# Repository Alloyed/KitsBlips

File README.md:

# KitsBlips

Monorepo for my Eurorack/synthesizer hobby projects! (that's me, I'm kit)

Everything is always in a state of "not-quite-finished". if something is unclear or unusable in its current state, and you want to use it, feel free to open an issue or contact me.

For technical reasons, this project is ordered by toolset and not by module. this means the full source for a single module may be across multiple folders! Sorry.

unless otherwise listed, all code is MIT licensed. All hardware designs and graphics (kicad, svg etc) are CC-BY-SA 4.0.

## Building/Installing

Each project/folder has a specific readme that includes extra steps if necessary, but in general, builds are managed using cmake.

```
$ mkdir -p <folder>/build && cd <folder>/build
$ cmake .. -DCMAKE_BUILD_TYPE=<build type: Debug, MinSizeRel, RelWithDebInfo>
$ cmake --build . --config=<the build type>
$ cmake --install . --prefix <location> # if the target supports installation
$ ctest # if the target has unit tests
```

once you have all your configurations set up, you can quickly rebuild all/run tests using `rebuild-all.sh`.

## Projects

For Hardware:

- [/daisy](daisy/README.md)
  - DSP code for hardware modules, using the Daisy microcontroller.
- [/kicad](kicad/README.md)
  - Hardware design files

For VCV Rack:

- [/vcvrack](daisy/README.md)
  - Modules for VCV Rack

For DAWS:

- [/daw](clap/README.md)
  - Modules for DAWS (VST3/CLAP plugins)
- [/clapeze](clapeze/README.md)
  - Microframework for writing clap plugins
- [/kitgui](kitgui/README.md)
  - UI library for clap plugins

Shared:

- [/panels](panels/README.md)
  - Art/Panel designs.
- [/kitdsp](kitdsp/README.md)
  - Shared DSP code, runs on all platforms
- [/kitdsp-gpl](kitdsp-gpl/README.md)
  - DSP code with GPL algorithms. This is the only folder that comes with extra license restrictions!

## AI statement

KitsBlips will not accept PRs that are generated wholly or in significant part by generative AI. Future development will not use Generative AI.

There are a few older commits where I tried it for automatic refactoring, found it less than successful, and cleaned it up afterward. You can try the same thing; I wouldn't be able to tell the difference probably, but my conclusion to that experiment was that it wasn't worth it at the time.

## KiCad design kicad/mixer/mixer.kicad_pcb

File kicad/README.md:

Kicad projects.

folders starting with `_`, eg `_design_rules` represent shared templates/libraries for all modules. all other folders are an individual module.

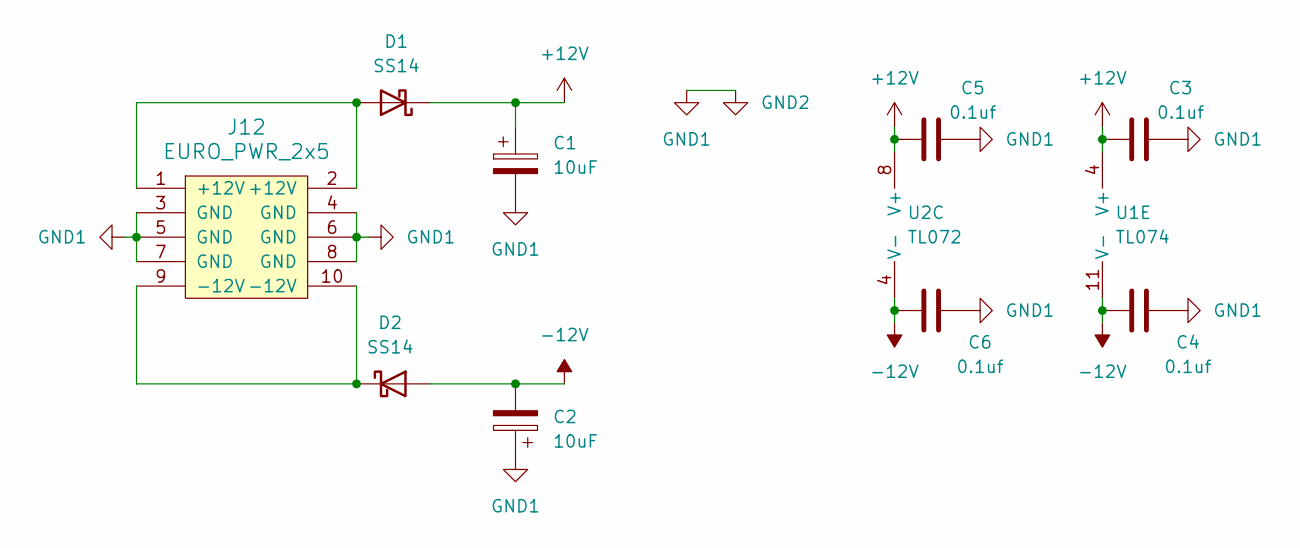
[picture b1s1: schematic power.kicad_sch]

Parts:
C1, C2: 10uF; C_0603_1608Metric_Pad1.08x0.95mm_HandSolder
C3, C4, C5, C6: 0.1uf; C_0603_1608Metric_Pad1.08x0.95mm_HandSolder
D1, D2: SS14; D_SMA
J12: EURO_PWR_2x5; Pins_2x05_2.54mm_TH_Europower_shrouded
U1: TL074; SOIC-14_3.9x8.7mm_P1.27mm
U2: TL072; SOIC-8_3.9x4.9mm_P1.27mm

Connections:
+12V: C1.1, C3.1, C5.1, D1.1 (K), U1.4 (V+), U2.8 (V+)
-12V: C2.2, C4.1, C6.1, D2.2 (A), U1.11 (V-), U2.4 (V-)
GND1: C1.2, C2.1, C3.2, C4.2, C5.2, C6.2, J12.3 (GND), J12.4 (GND), J12.5 (GND), J12.6 (GND), J12.7 (GND), J12.8 (GND); also elsewhere on the board
unnamed: D1.2 (A), J12.1 (+12V), J12.2 (+12V)
unnamed: D2.1 (K), J12.9 (-12V), J12.10 (-12V)

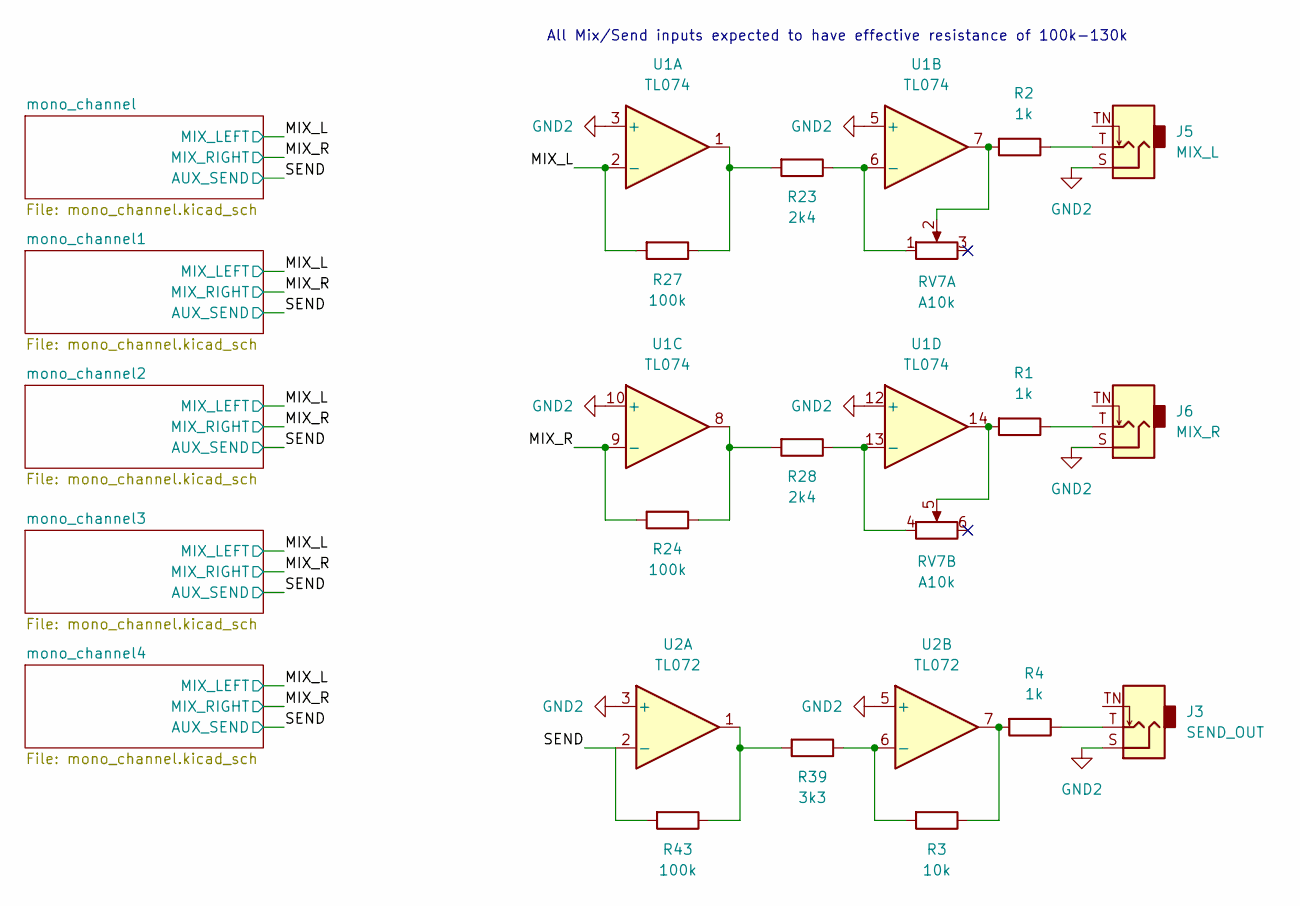
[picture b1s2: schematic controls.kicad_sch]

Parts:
J3: SEND_OUT; Jack_3.5mm_QingPu_WQP-PJ398SM_Vertical_CircularHoles
J5: MIX_L; Jack_3.5mm_QingPu_WQP-PJ398SM_Vertical_CircularHoles
J6: MIX_R; Jack_3.5mm_QingPu_WQP-PJ398SM_Vertical_CircularHoles
R1, R2, R4: 1k; R_0603_1608Metric_Pad0.98x0.95mm_HandSolder
R3: 10k; R_0603_1608Metric_Pad0.98x0.95mm_HandSolder
R23, R28: 2k4; R_0603_1608Metric_Pad0.98x0.95mm_HandSolder
R24, R27, R43: 100k; R_0603_1608Metric_Pad0.98x0.95mm_HandSolder
R39: 3k3; R_0603_1608Metric_Pad0.98x0.95mm_HandSolder
RV7: A10k; Potentiometer_Alpha_RD902F-40-00D_Dual_Vertical
U1: TL074; SOIC-14_3.9x8.7mm_P1.27mm
U2: TL072; SOIC-8_3.9x4.9mm_P1.27mm

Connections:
/controls/MIX_L: R27.2, U1.2 (-); also elsewhere on the board
/controls/MIX_R: R24.2, U1.9 (-); also elsewhere on the board
/controls/SEND: R43.2, U2.2 (-); also elsewhere on the board
GND1: J3.S, J5.S, J6.S, U1.3 (+), U1.5 (+), U1.10 (+), U1.12 (+), U2.3 (+), U2.5 (+); also elsewhere on the board
unnamed: J3.T, R4.1
unnamed: J5.T, R2.1
unnamed: J6.T, R1.1
unnamed: R1.2, RV7.5, U1.14
unnamed: R2.2, RV7.2, U1.7
unnamed: R3.1, R4.2, U2.7
unnamed: R23.2, R27.1, U1.1
unnamed: R24.1, R28.2, U1.8
unnamed: R39.2, R43.1, U2.1
unnamed: R23.1, RV7.1, U1.6 (-)
unnamed: R28.1, RV7.4, U1.13 (-)
unnamed: R3.2, R39.1, U2.6 (-)

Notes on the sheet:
All Mix/Send inputs expected to have effective resistance of 100k-130k

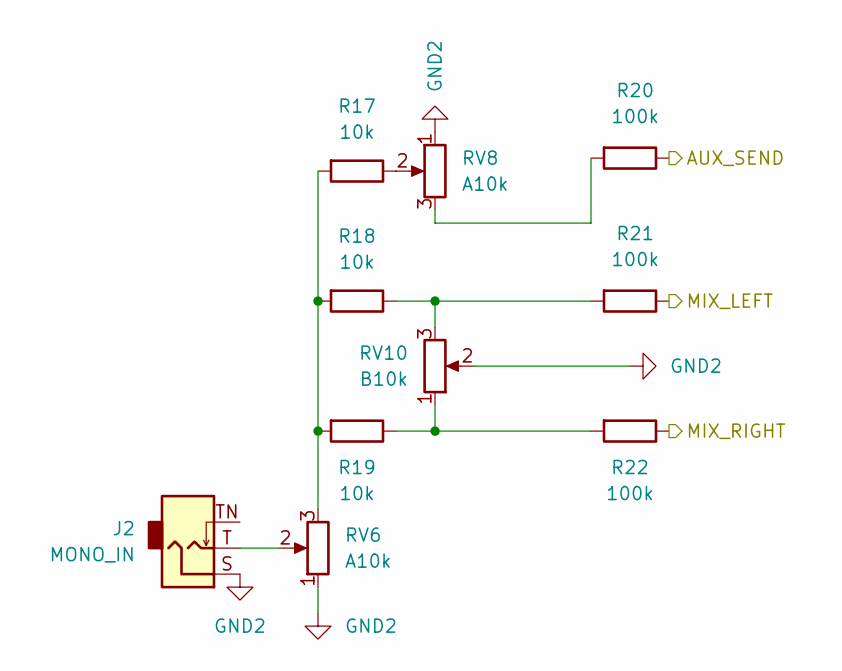
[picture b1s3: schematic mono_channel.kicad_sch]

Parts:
J2: MONO_IN; Jack_3.5mm_QingPu_WQP-PJ398SM_Vertical_CircularHoles
R17, R18, R19: 10k; R_0603_1608Metric_Pad0.98x0.95mm_HandSolder
R20, R21, R22: 100k; R_0603_1608Metric_Pad0.98x0.95mm_HandSolder
RV6, RV8: A10k; Potentiometer_Alpha_RD901F-40-00D_Single_Vertical
RV10: B10k; Potentiometer_Alpha_RD901F-40-00D_Single_Vertical

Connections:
/controls/MIX_L: R21.1; also elsewhere on the board
/controls/MIX_R: R22.1; also elsewhere on the board
/controls/SEND: R20.1; also elsewhere on the board
GND1: J2.S, RV6.1, RV8.1, RV10.2; also elsewhere on the board
unnamed: J2.T, RV6.2
unnamed: R17.1, RV8.2
unnamed: R17.2, R18.2, R19.2, RV6.3
unnamed: R18.1, R21.2, RV10.3
unnamed: R19.1, R22.2, RV10.1
unnamed: R20.2, RV8.3

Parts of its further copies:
J1, J4, J7, J8: MONO_IN; Jack_3.5mm_QingPu_WQP-PJ398SM_Vertical_CircularHoles
R5, R6, R7, R8, R9, R13, R25, R26, R29, R33, R34, R35: 10k; R_0603_1608Metric_Pad0.98x0.95mm_HandSolder
R10, R11, R12, R14, R15, R16, R30, R31, R32, R36, R37, R38: 100k; R_0603_1608Metric_Pad0.98x0.95mm_HandSolder
RV1, RV2, RV4, RV9, RV11, RV12, RV14, RV15: A10k; Potentiometer_Alpha_RD901F-40-00D_Single_Vertical
RV3, RV5, RV13, RV16: B10k; Potentiometer_Alpha_RD901F-40-00D_Single_Vertical

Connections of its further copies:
/controls/MIX_L: R11.1, R15.1, R31.1, R37.1; also elsewhere on the board
/controls/MIX_R: R12.1, R16.1, R32.1, R38.1; also elsewhere on the board
/controls/SEND: R10.1, R14.1, R30.1, R36.1; also elsewhere on the board
GND1: J1.S, J4.S, J7.S, J8.S, RV1.1, RV2.1, RV3.2, RV4.1, RV5.2, RV9.1, RV11.1, RV12.1, RV13.2, RV14.1, RV15.1, RV16.2; also elsewhere on the board
unnamed: J1.T, RV2.2
unnamed: J4.T, RV11.2
unnamed: J7.T, RV1.2
unnamed: J8.T, RV14.2
unnamed: R5.1, RV4.2
unnamed: R7.1, RV9.2
unnamed: R7.2, R8.2, R9.2, RV1.3
unnamed: R10.2, RV9.3
unnamed: R8.1, R11.2, RV3.3
unnamed: R9.1, R12.2, RV3.1
unnamed: R13.1, R16.2, RV5.1
unnamed: R5.2, R6.2, R13.2, RV2.3
unnamed: R14.2, RV4.3
unnamed: R6.1, R15.2, RV5.3
unnamed: R25.1, RV12.2
unnamed: R25.2, R26.2, R29.2, RV11.3
unnamed: R26.1, R31.2, RV13.3
unnamed: R29.1, R32.2, RV13.1
unnamed: R30.2, RV12.3
unnamed: R33.1, RV15.2
unnamed: R33.2, R34.2, R35.2, RV14.3
unnamed: R34.1, R37.2, RV16.3
unnamed: R35.1, R38.2, RV16.1
unnamed: R36.2, RV15.3

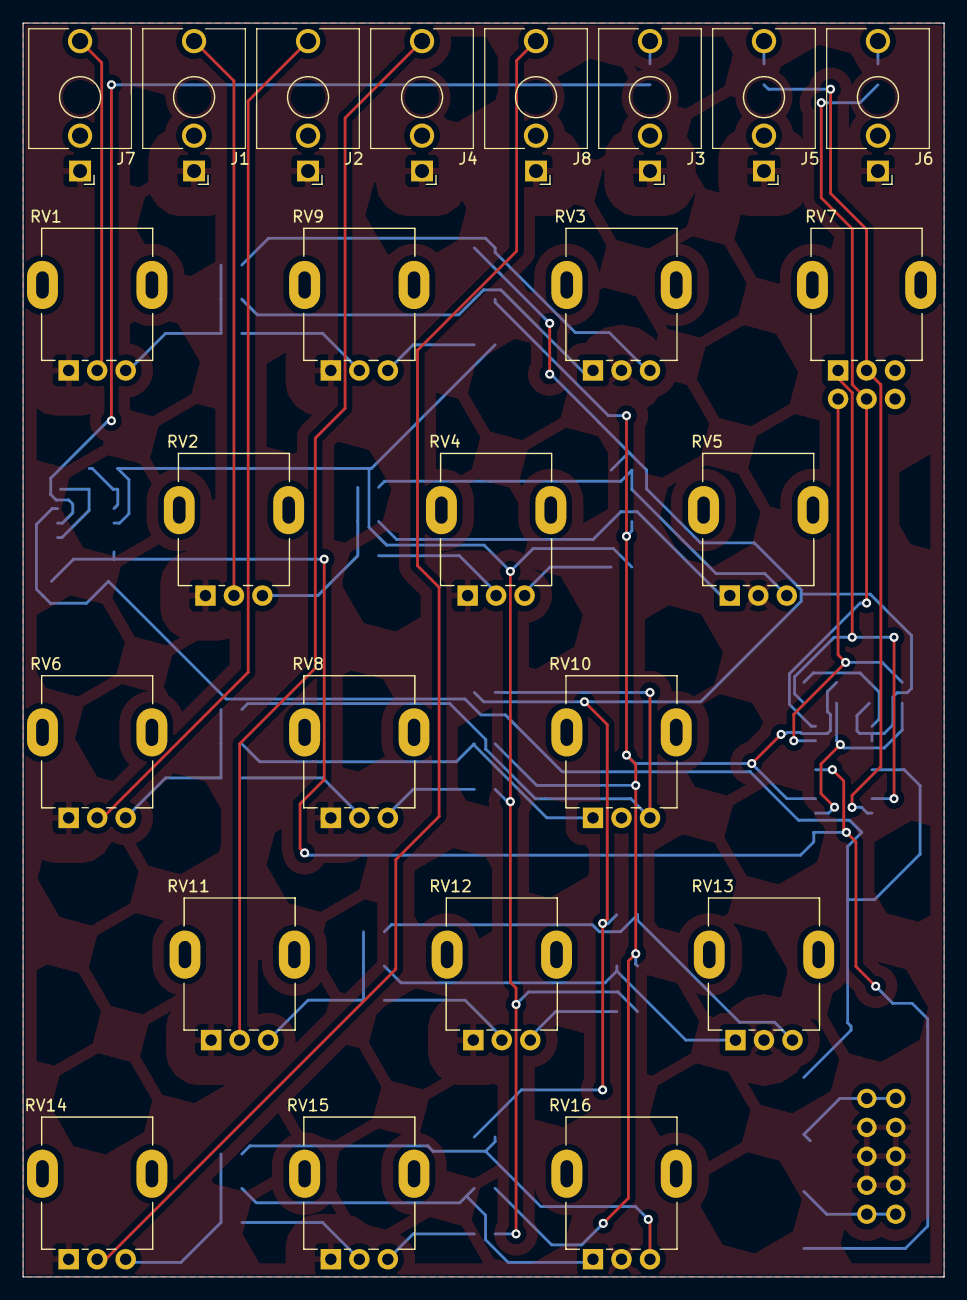
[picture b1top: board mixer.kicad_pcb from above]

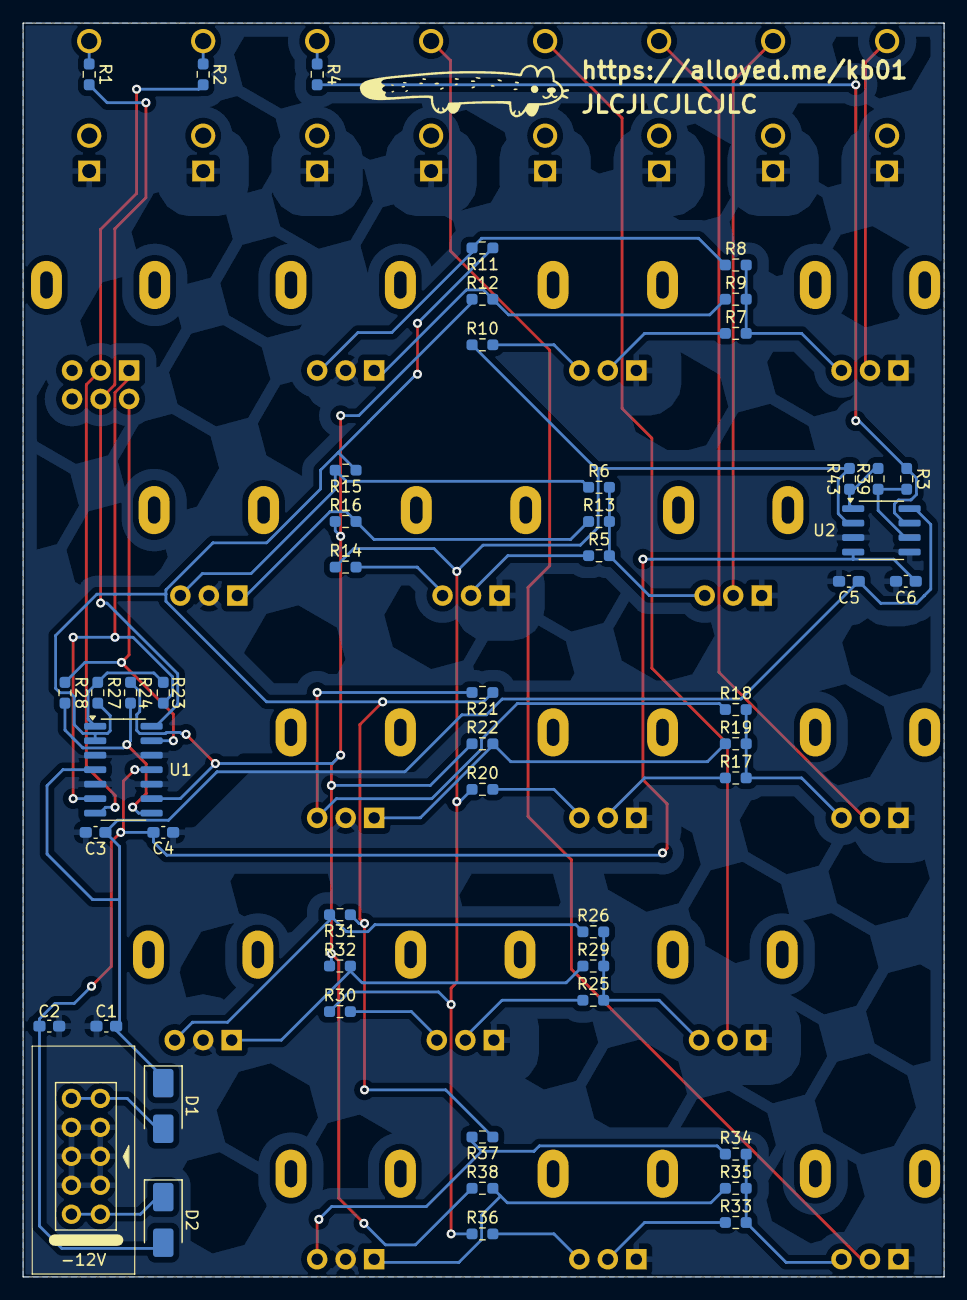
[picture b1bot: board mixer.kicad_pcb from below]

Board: 2 copper layers, 80.8 x 110.0 mm, 75 parts (51 on the bottom side), 50 nets.

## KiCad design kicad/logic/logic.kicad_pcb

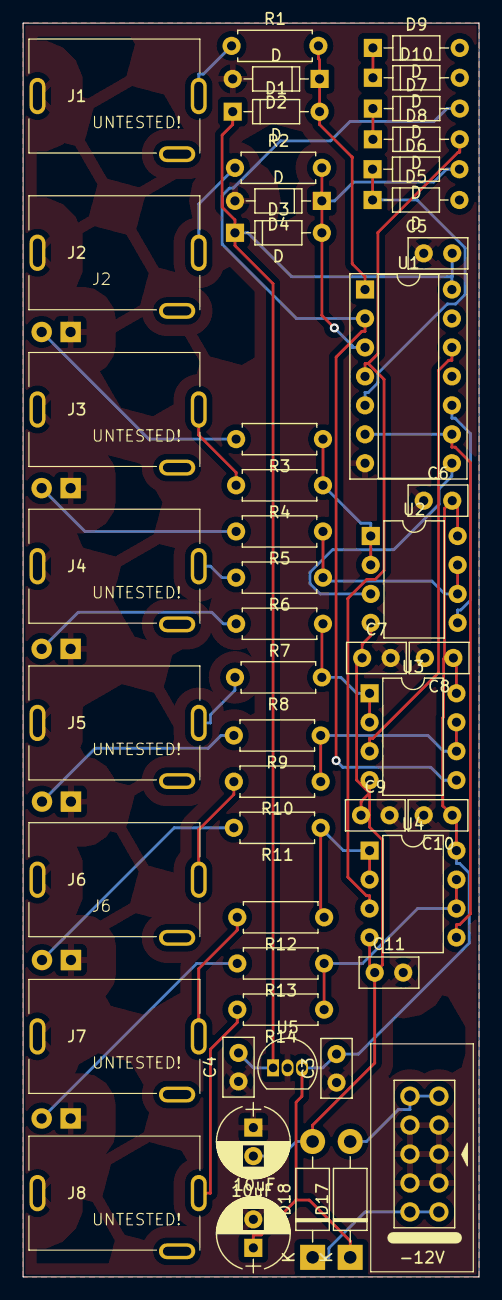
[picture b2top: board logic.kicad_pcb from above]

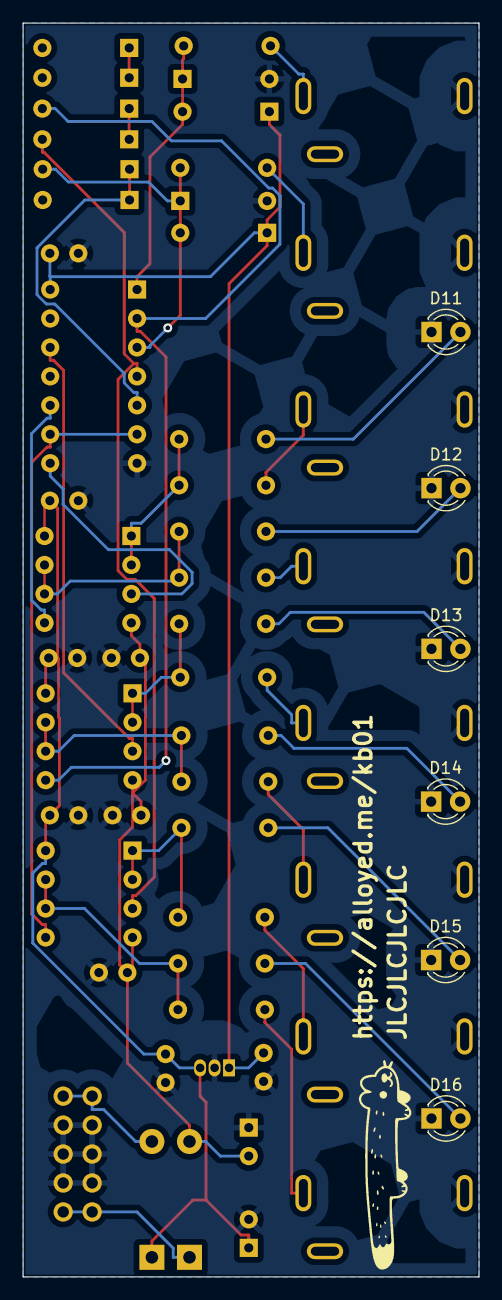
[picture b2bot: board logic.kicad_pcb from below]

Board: 2 copper layers, 40.0 x 110.0 mm, 57 parts (6 on the bottom side), 37 nets.

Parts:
C1, C2: 10uF; CP_Radial_P2.5mm
C3: 0.33uf; C_Disc_D5.0mm_W2.5mm_P2.50mm
C4, C5, C6, C7, C8, C9, C10, C11: 0.1uf; C_Disc_D5.0mm_W2.5mm_P2.50mm
D1, D2, D3, D4, D5, D6, D7, D8, D9, D10: D; D_DO-35_P7.62mm_Horizontal
D11, D12, D13, D14, D15, D16: LED; LED_D3.0mm
D17, D18: 1N5819; D_DO-41_SOD81_P10.16mm_Horizontal
J1: A_IN; Jack_3.5mm_Thonk_Mono_Horizontal_WQP729JH
J2: B_IN; Jack_3.5mm_Thonk_Mono_Horizontal_WQP729JH
J3: A_OR_B_OUT; Jack_3.5mm_Thonk_Mono_Horizontal_WQP729JH
J4: A_AND_B_OUT; Jack_3.5mm_Thonk_Mono_Horizontal_WQP729JH
J5: A_XOR_B_OUT; Jack_3.5mm_Thonk_Mono_Horizontal_WQP729JH
J6: NOT_A_OUT; Jack_3.5mm_Thonk_Mono_Horizontal_WQP729JH
J7: NOT_B_OUT; Jack_3.5mm_Thonk_Mono_Horizontal_WQP729JH
J8: A_NOR_B_OUT; Jack_3.5mm_Thonk_Mono_Horizontal_WQP729JH
J9: EURO_PWR_2x5; Pins_2x05_2.54mm_TH_Europower_shrouded
R1, R2: 100k; R_Axial_DIN0207_L6.3mm_D2.5mm_P7.62mm_Horizontal
R3, R5, R7, R9, R11, R13: 3k; R_Axial_DIN0207_L6.3mm_D2.5mm_P7.62mm_Horizontal
R4, R6, R8, R10, R12, R14: 1k; R_Axial_DIN0207_L6.3mm_D2.5mm_P7.62mm_Horizontal
U1: 40106; DIP-14_W7.62mm_Socket
U2, U3, U4: TL072; DIP-8_W7.62mm
U5: L78L05_TO92; TO-92_Inline

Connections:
+5V: C4.2, C5.1, D1.1 (K), D3.1 (K), U1.14 (VDD), U5.1 (VO)
+12V: C1.1, C3.2, C6.1, C8.1, C10.1, D17.1 (K), U2.8 (V+), U3.8 (V+), U4.8 (V+), U5.3 (VI)
-12V: C2.2, C7.1, C9.1, C11.1, D18.2 (A), U2.4 (V-), U3.4 (V-), U4.4 (V-)
/A: D1.2 (A), D2.1 (K), D5.2 (A), R1.2, U1.1
/A_AND_B: D10.2 (A), U1.10, U2.5 (+)
/A_NOR_B: D9.2 (A), U1.6, U1.9, U4.5 (+)
/A_OR_B: U1.8, U2.3 (+)
/A_XOR_B: U1.12, U3.3 (+)
/B: D3.2 (A), D4.1 (K), D6.2 (A), R2.2, U1.3
/NOT_A: D7.2 (A), U1.2, U3.5 (+)
/NOT_B: D8.2 (A), U1.4, U4.3 (+)
GND1: C1.2, C2.1, C3.1, C4.1, C5.2, C6.2, C7.2, C8.2, C9.2, C10.2, C11.2, D2.2 (A), D4.2 (A), D11.1 (K), D12.1 (K), D13.1 (K), D14.1 (K), D15.1 (K), D16.1 (K), J1.S, J2.S, J3.S, J4.S, J5.S, J6.S, J7.S, J8.S, J9.3 (GND), J9.4 (GND), J9.5 (GND), J9.6 (GND), J9.7 (GND), J9.8 (GND), U1.7 (VSS), U5.2 (GND)
unnamed: D5.1 (K), D6.1 (K), U1.5
unnamed: D7.1 (K), D8.1 (K), U1.11
unnamed: D9.1 (K), D10.1 (K), U1.13
unnamed: D11.2 (A), R3.2
unnamed: D12.2 (A), R5.2
unnamed: D13.2 (A), R7.2
unnamed: D14.2 (A), R9.2
unnamed: D15.2 (A), R11.2
unnamed: D16.2 (A), R13.2
unnamed: D17.2 (A), J9.1 (+12V), J9.2 (+12V)
unnamed: D18.1 (K), J9.9 (-12V), J9.10 (-12V)
unnamed: J1.T, R1.1
unnamed: J2.T, R2.1
unnamed: J3.T, R4.2
unnamed: J4.T, R6.2
unnamed: J5.T, R8.2
unnamed: J6.T, R10.2
unnamed: J7.T, R12.2
unnamed: J8.T, R14.2
unnamed: R3.1, R4.1, U2.1, U2.2 (-)
unnamed: R5.1, R6.1, U2.6 (-), U2.7
unnamed: R7.1, R8.1, U3.1, U3.2 (-)
unnamed: R9.1, R10.1, U3.6 (-), U3.7
unnamed: R11.1, R12.1, U4.1, U4.2 (-)
unnamed: R13.1, R14.1, U4.6 (-), U4.7

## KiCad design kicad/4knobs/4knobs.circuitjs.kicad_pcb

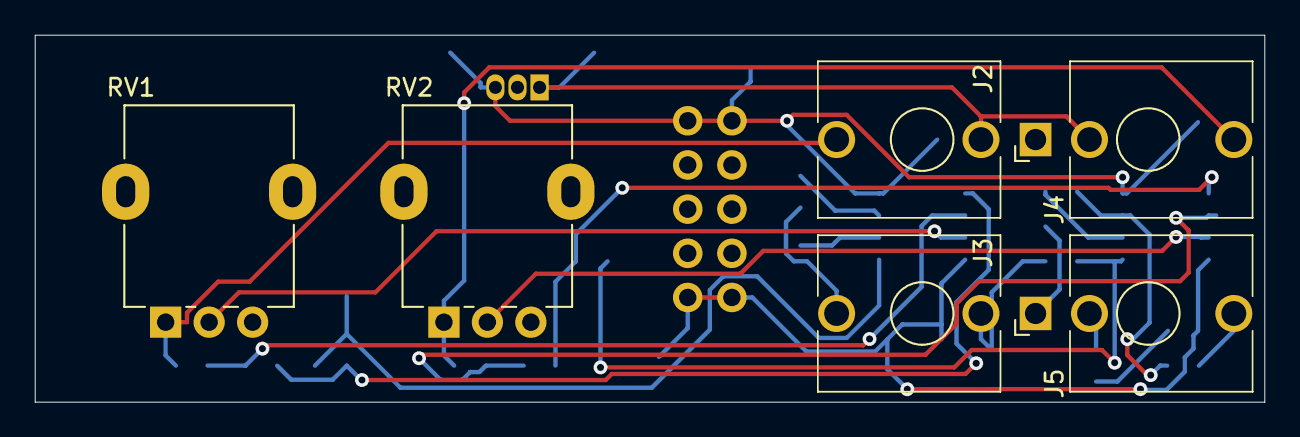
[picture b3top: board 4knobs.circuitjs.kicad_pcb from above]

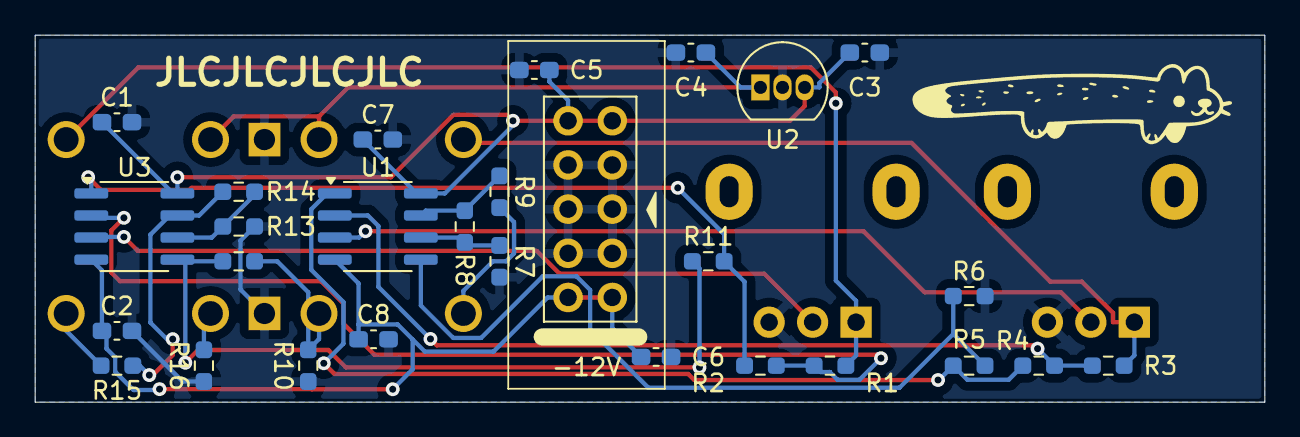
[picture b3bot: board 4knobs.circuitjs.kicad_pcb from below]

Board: 2 copper layers, 70.7 x 21.1 mm, 34 parts (28 on the bottom side), 22 nets.

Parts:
C1, C2, C4, C7, C8: 0.1uf; C_0603_1608Metric_Pad1.08x0.95mm_HandSolder
C3: 0.33uf; C_0603_1608Metric_Pad1.08x0.95mm_HandSolder
C5, C6: 10uF; C_0603_1608Metric_Pad1.08x0.95mm_HandSolder
J1: EURO_PWR_2x5; Pins_2x05_2.54mm_TH_Europower_shrouded
J2, J4: IN; Jack_3.5mm_QingPu_WQP-PJ398SM_Vertical_CircularHoles
J3, J5: OUT; Jack_3.5mm_QingPu_WQP-PJ398SM_Vertical_CircularHoles
R1, R2, R3, R4: 20k; R_0603_1608Metric_Pad0.98x0.95mm_HandSolder
R5, R6, R11, R12: 100k; R_0603_1608Metric_Pad0.98x0.95mm_HandSolder
R7, R8, R13, R14: 10k; R_0603_1608Metric_Pad0.98x0.95mm_HandSolder
R9, R15: 220R; R_0603_1608Metric_Pad0.98x0.95mm_HandSolder
R10, R16: 1M; R_0603_1608Metric_Pad0.98x0.95mm_HandSolder
RV1, RV2: B10k; Potentiometer_Alpha_RD901F-40-00D_Single_Vertical
U1, U3: TL072; SOIC-8_3.9x4.9mm_P1.27mm
U2: L78L05_TO92; TO-92_Inline

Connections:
+5V: C4.1, J2.TN, J4.TN, U2.1 (VO)
+12V: C1.1, C3.1, C5.1, C7.1, J1.1 (+12V), J1.2 (+12V), U1.8 (V+), U2.3 (VI), U3.8 (V+)
-12V: C2.1, C6.2, C8.1, J1.9 (-12V), J1.10 (-12V), U1.4 (V-), U3.4 (V-)
/controls/channel1/MIX_OUT: J5.TN, R16.2
/controls/channel/MIX_OUT: J3.TN, R10.2, R12.2
GND1: C1.2, C2.2, C3.2, C4.2, C5.2, C6.1, C7.2, C8.2, J1.3 (GND), J1.4 (GND), J1.5 (GND), J1.6 (GND), J1.7 (GND), J1.8 (GND), J4.S, J5.S, R6.2, R7.2, R10.1, R13.2, R16.1, RV1.3, RV2.3, U2.2 (GND)
unnamed: J2.T, R3.2, RV1.1
unnamed: J3.T, R9.2
unnamed: J4.T, R1.2, RV2.1
unnamed: J5.T, R15.2
unnamed: R4.1, R5.2, U1.1
unnamed: R8.1, R9.1, U1.7
unnamed: R2.1, R11.2, U3.1
unnamed: R14.1, R15.1, U3.7
unnamed: RV1.2, U1.3 (+)
unnamed: R3.1, R4.2, U1.2 (-)
unnamed: R5.1, R6.1, U1.5 (+)
unnamed: R7.1, R8.2, U1.6 (-)
unnamed: RV2.2, U3.3 (+)
unnamed: R1.1, R2.2, U3.2 (-)
unnamed: R11.1, R12.1, U3.5 (+)
unnamed: R13.1, R14.2, U3.6 (-)

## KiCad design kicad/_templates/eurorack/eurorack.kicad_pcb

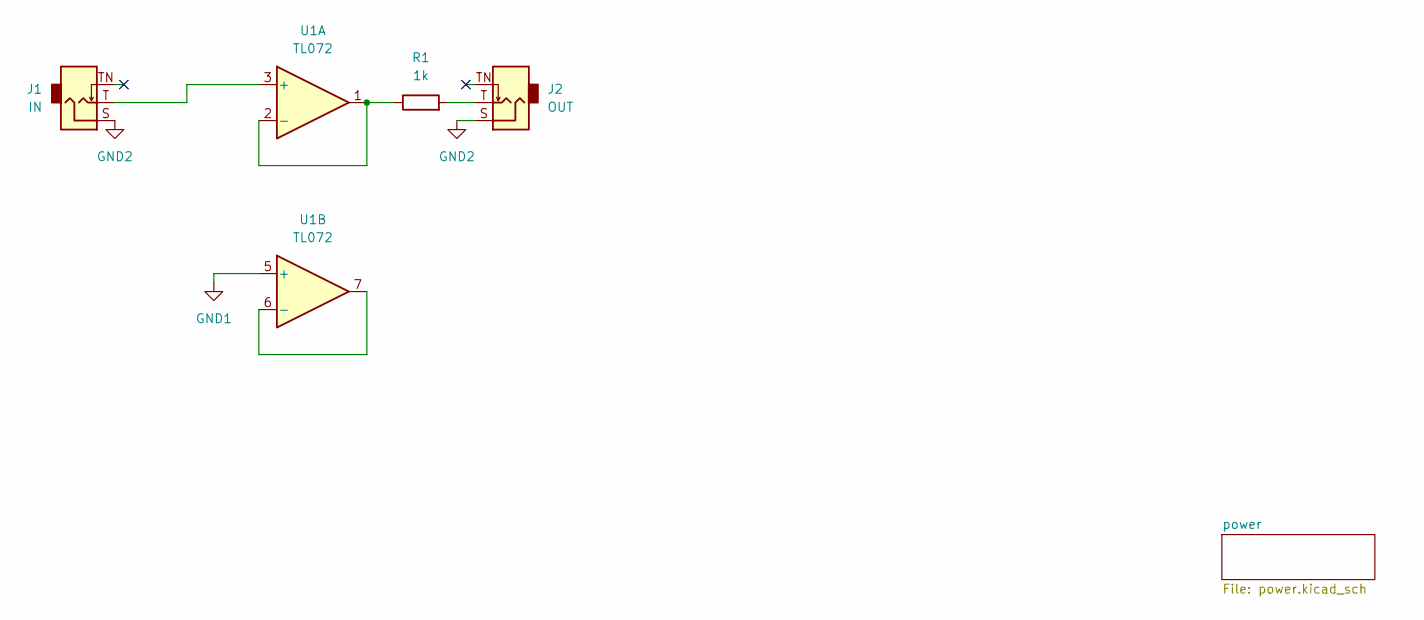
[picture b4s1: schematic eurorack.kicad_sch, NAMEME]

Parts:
J1: IN; Jack_3.5mm_QingPu_WQP-PJ398SM_Vertical_CircularHoles
J2: OUT; Jack_3.5mm_QingPu_WQP-PJ398SM_Vertical_CircularHoles
R1: 1k; R_Axial_DIN0207_L6.3mm_D2.5mm_P7.62mm_Horizontal
U1: TL072; DIP-8_W7.62mm_LongPads

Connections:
GND1: J1.S, J2.S, U1.5 (+); also elsewhere on the board
unnamed: J2.T, R1.2
unnamed: J1.T, U1.3 (+)
unnamed: R1.1, U1.1, U1.2 (-)
unnamed: U1.6 (-), U1.7

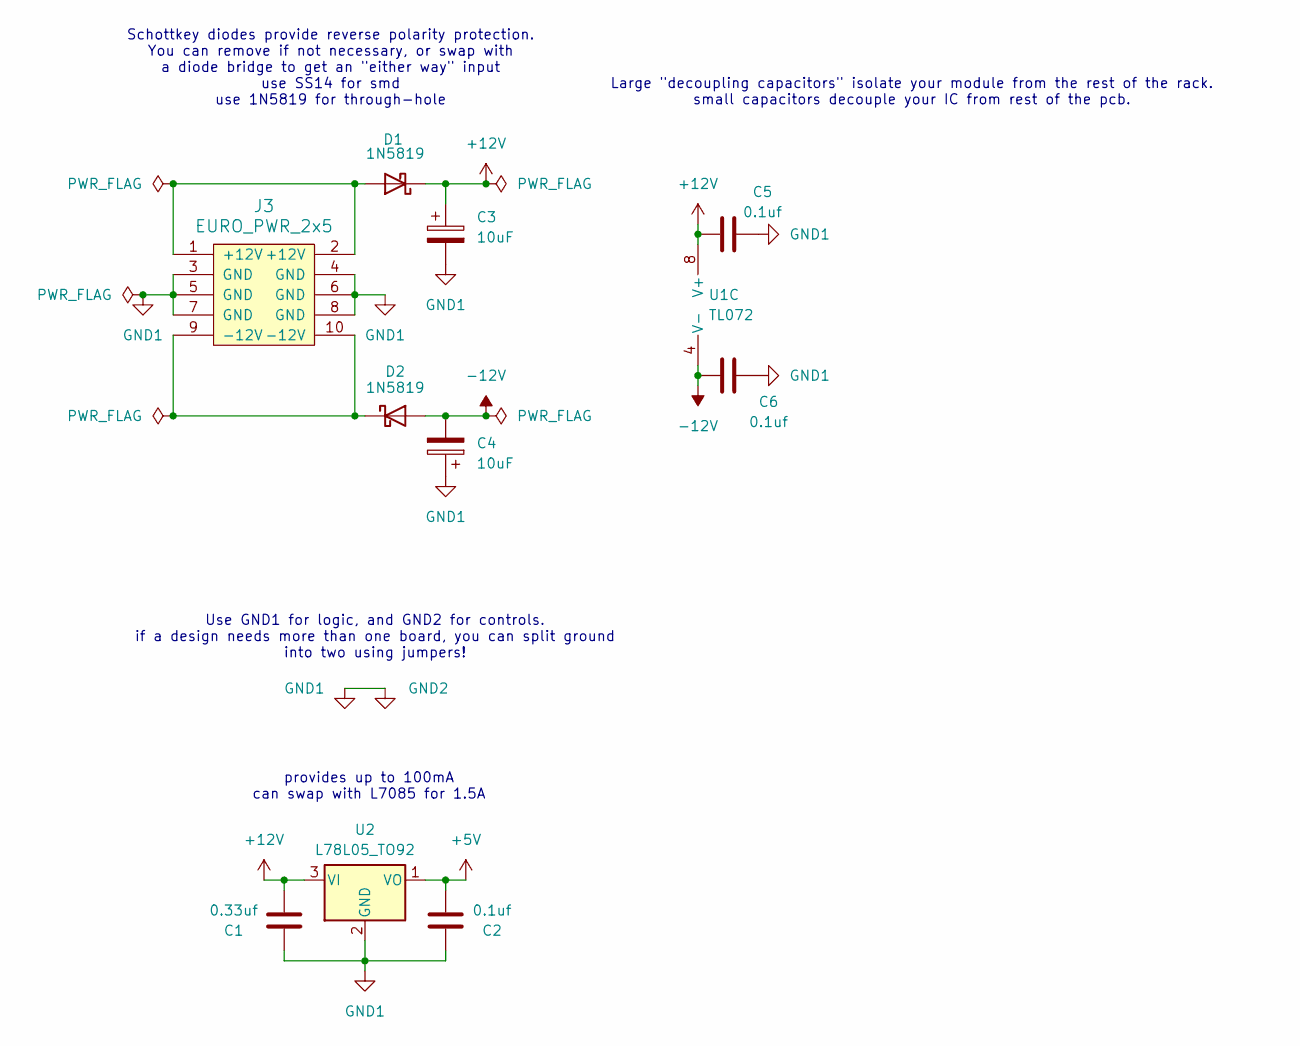
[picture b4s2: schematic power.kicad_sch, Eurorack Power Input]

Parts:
C1: 0.33uf; C_Disc_D5.0mm_W2.5mm_P2.50mm
C2, C5, C6: 0.1uf; C_Disc_D5.0mm_W2.5mm_P2.50mm
C3, C4: 10uF; CP_Radial_P2.5mm
D1, D2: 1N5819; D_DO-41_SOD81_P10.16mm_Horizontal
J3: EURO_PWR_2x5; Pins_2x05_2.54mm_TH_Europower_shrouded
U1: TL072; DIP-8_W7.62mm_LongPads
U2: L78L05_TO92; TO-92_Inline

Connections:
+5V: C2.2, U2.1 (VO)
+12V: C1.2, C3.1, C5.1, D1.1 (K), U1.8 (V+), U2.3 (VI)
-12V: C4.2, C6.1, D2.2 (A), U1.4 (V-)
GND1: C1.1, C2.1, C3.2, C4.1, C5.2, C6.2, J3.3 (GND), J3.4 (GND), J3.5 (GND), J3.6 (GND), J3.7 (GND), J3.8 (GND), U2.2 (GND); also elsewhere on the board
unnamed: D1.2 (A), J3.1 (+12V), J3.2 (+12V)
unnamed: D2.1 (K), J3.9 (-12V), J3.10 (-12V)

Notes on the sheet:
Large "decoupling capacitors" isolate your module from the rest of the rack. small capacitors decouple your IC from rest of the pcb.
Use GND1 for logic, and GND2 for controls. if a design needs more than one board, you can split ground into two using jumpers!
Schottkey diodes provide reverse polarity protection. You can remove if not necessary, or swap with a diode bridge to get an "either way" input use SS14 for smd use 1N5819 for through-hole
provides up to 100mA can swap with L7085 for 1.5A

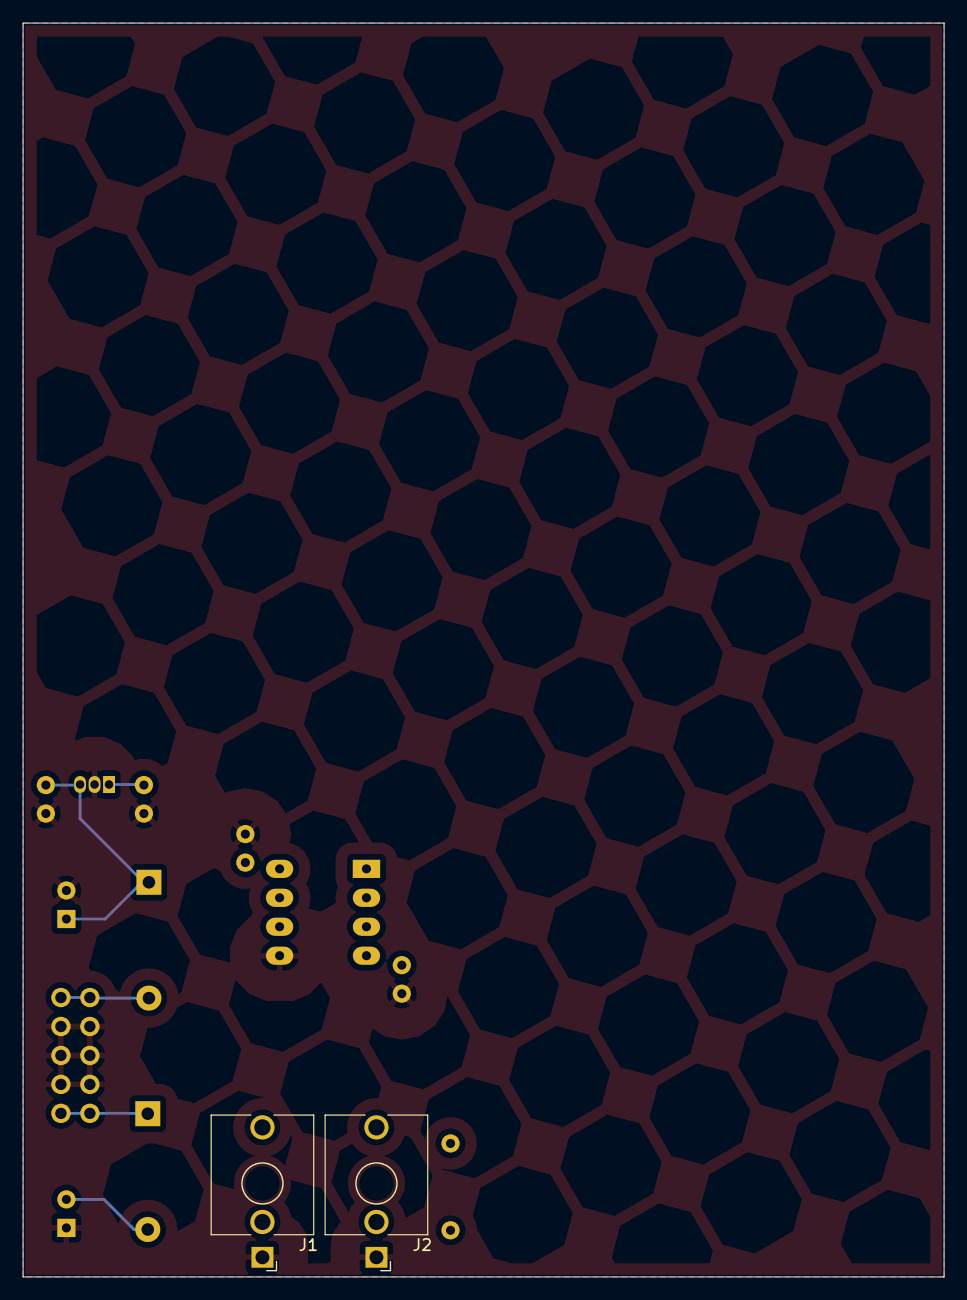
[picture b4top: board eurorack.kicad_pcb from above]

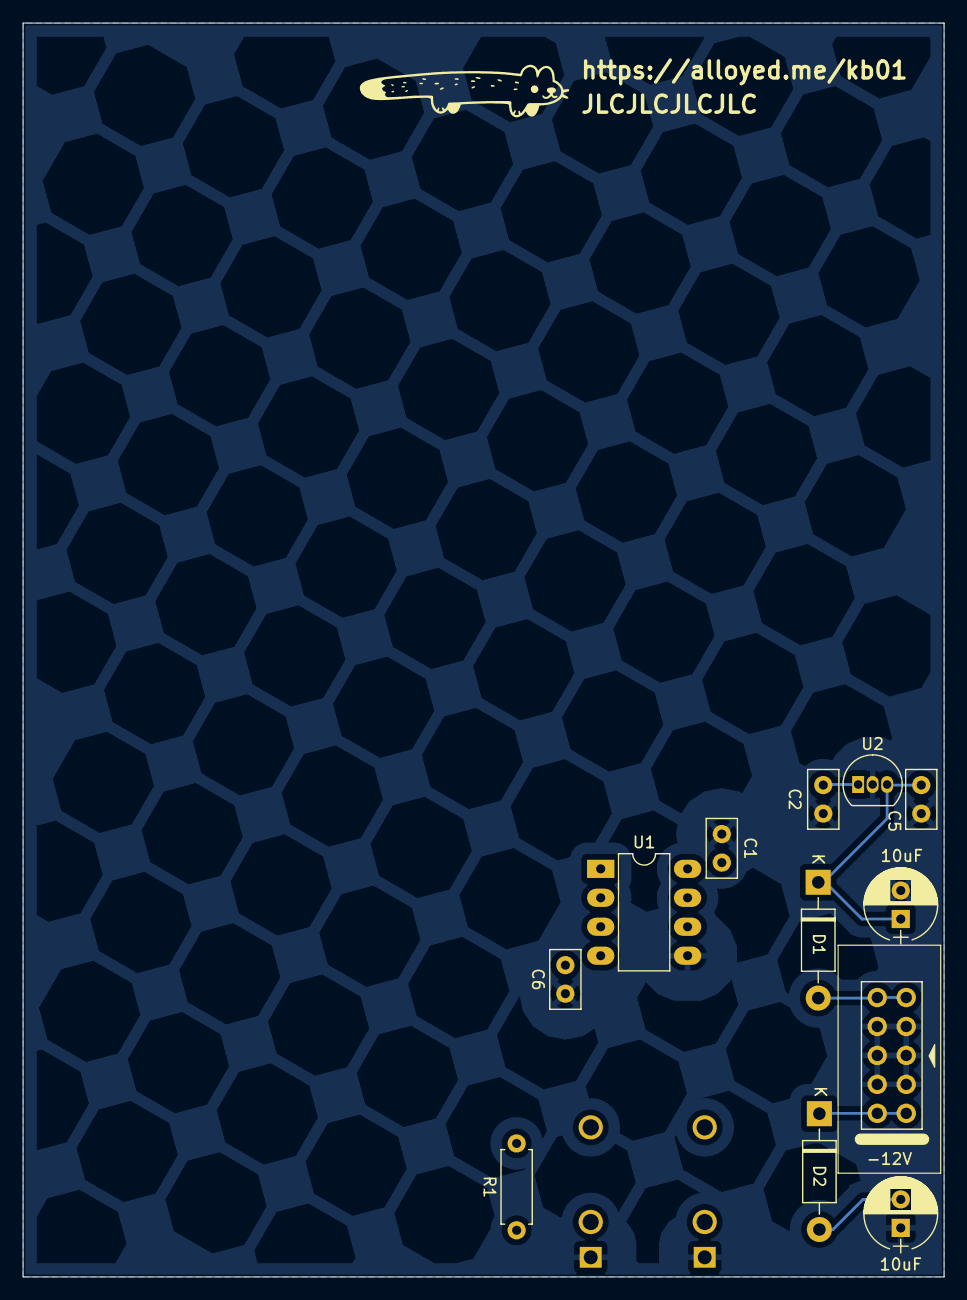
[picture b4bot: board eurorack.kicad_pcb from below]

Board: 2 copper layers, 80.8 x 110.0 mm, 14 parts (12 on the bottom side), 10 nets.

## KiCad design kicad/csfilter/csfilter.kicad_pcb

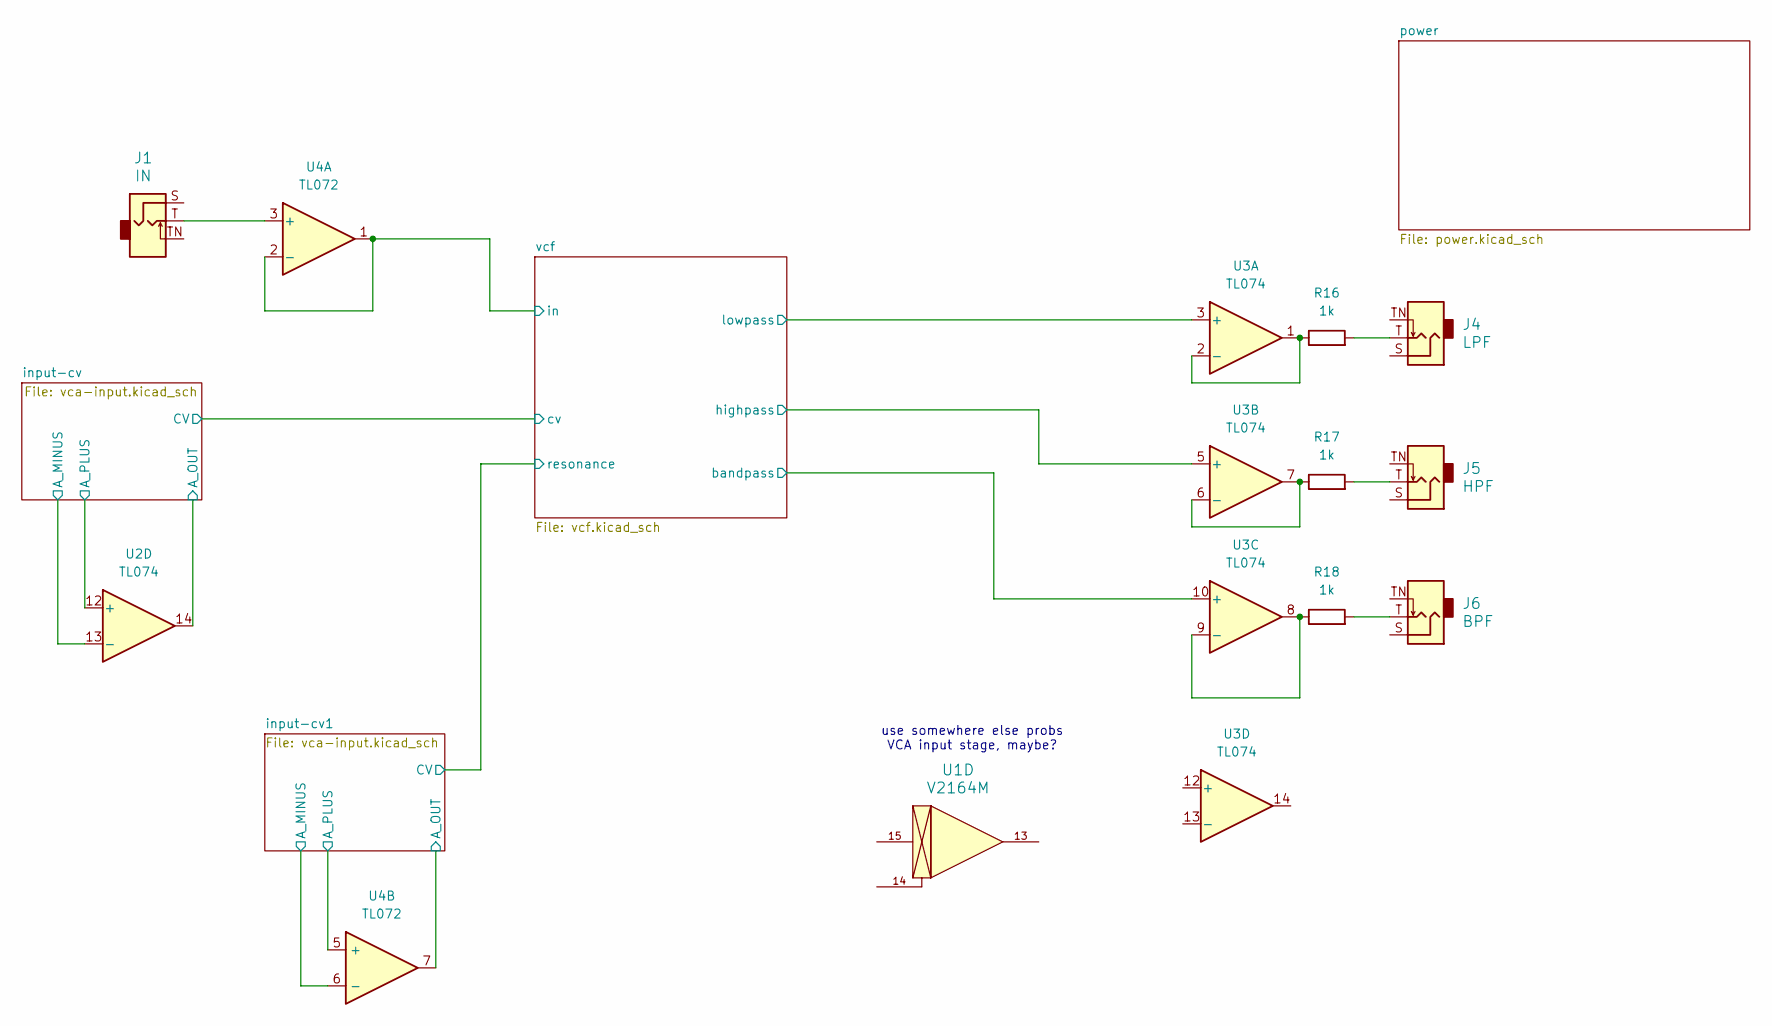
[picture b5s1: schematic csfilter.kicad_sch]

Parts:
J1: IN; Jack_3.5mm_QingPu_WQP-PJ398SM_Vertical_CircularHoles; Part Number WQP-WQP518MA
J4: LPF; Jack_3.5mm_QingPu_WQP-PJ398SM_Vertical_CircularHoles; Part Number WQP-WQP518MA
J5: HPF; Jack_3.5mm_QingPu_WQP-PJ398SM_Vertical_CircularHoles; Part Number WQP-WQP518MA
J6: BPF; Jack_3.5mm_QingPu_WQP-PJ398SM_Vertical_CircularHoles; Part Number WQP-WQP518MA
R16, R17, R18: 1k; R_Axial_DIN0207_L6.3mm_D2.5mm_P7.62mm_Horizontal
U1: V2164M; DIP-16_W7.62mm_Socket
U2, U3: TL074; DIP-14_W7.62mm_Socket
U4: TL072; DIP-8_W7.62mm_Socket

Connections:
/input-cv1/A_MINUS: U4.6 (-); also elsewhere on the board
/input-cv1/A_OUT: U4.7; also elsewhere on the board
/input-cv/A_MINUS: U2.13 (-); also elsewhere on the board
/input-cv/A_OUT: U2.14; also elsewhere on the board
/vcf/bandpass: U3.10 (+); also elsewhere on the board
/vcf/in: U4.1, U4.2 (-); also elsewhere on the board
/vcf/lowpass: U3.3 (+); also elsewhere on the board
GND1: U2.12 (+), U4.5 (+); also elsewhere on the board
unnamed: J4.T, R16.2
unnamed: J5.T, R17.2
unnamed: J6.T, R18.2
unnamed: R16.1, U3.1, U3.2 (-)
unnamed: R17.1, U3.6 (-), U3.7
unnamed: R18.1, U3.8, U3.9 (-)
unnamed: J1.T, U4.3 (+)

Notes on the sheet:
use somewhere else probs VCA input stage, maybe?

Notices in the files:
kicad/stylophone/stylophone-1968.kicad_pcb:
CC-BY-SA 4.0 2024
kicad/stylophone/stylophone-1968.kicad_sch:
(c) 2023 Simon Inns
License: Attribution-ShareAlike 4.0 International (CC BY-SA 4.0)
